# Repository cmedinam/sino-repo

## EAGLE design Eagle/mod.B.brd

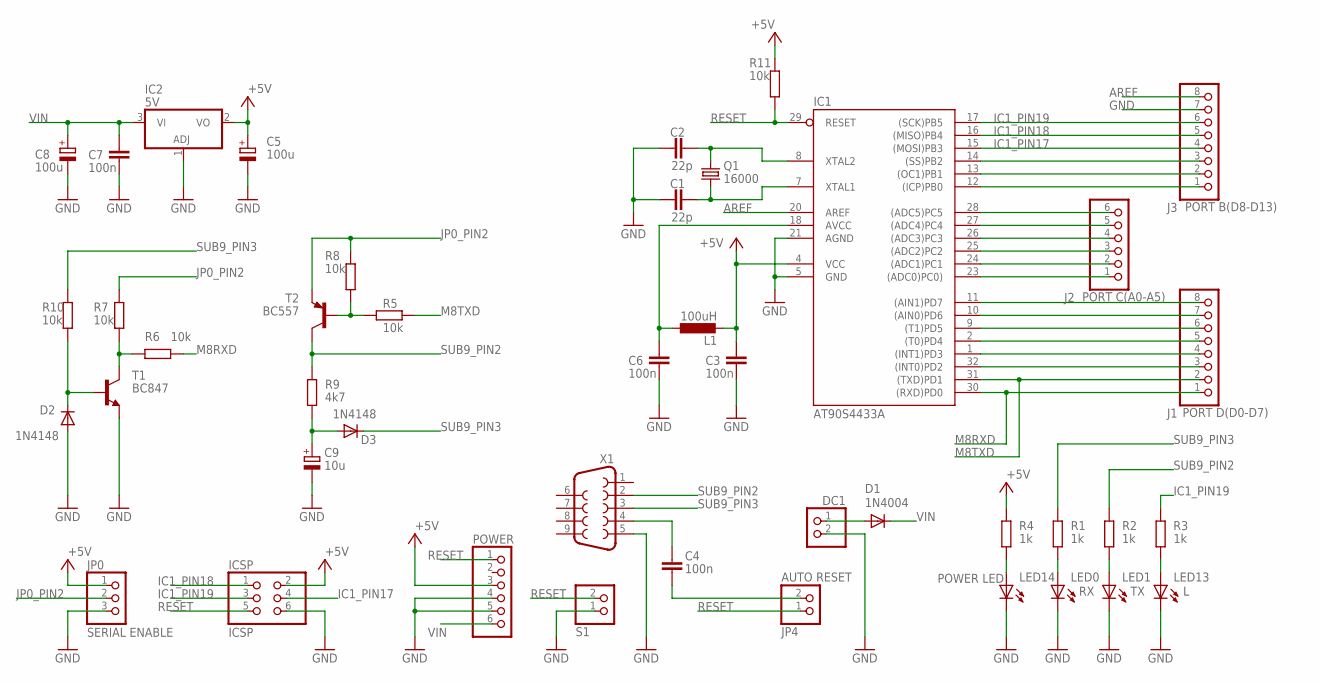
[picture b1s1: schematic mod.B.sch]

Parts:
C1, C2: 22p; C0805
C3, C4, C6, C7: 100n; C0805
C5, C8: 100u; PANASONIC_D
C9: 10u; PANASONIC_B
D1: 1N4004; SOD80C
D2, D3: 1N4148; SOD80C
DC1: PINHD-1X2; 1X02
IC1: AT90S4433A; TQFP32-08
IC2: 5V; SOT223
ICSP: ICSP; 2X03
J1: PORT D(D0-D7); 1X08
J2: PORT C(A0-A5); 1X06
J3: PORT B(D8-D13); 1X08
JP0: SERIAL ENABLE; 1X03
JP4: AUTO RESET; 1X02
L1: 100uH; L1812
LED0: RX; CHIP-LED0603
LED1: TX; CHIP-LED0603
LED13: L; CHIP-LED0603
LED14: POWER LED; CHIP-LED0603
POWER: PINHD-1X6; 1X06
Q1: 16000; SM49
R1, R2, R3, R4: 1k; M0805
R5, R6, R7, R8, R10, R11: 10k; M0805
R9: 4k7; R1206
S1: PINHD-1X2; 1X02
T1: BC847; SOT23
T2: BC557; SOT23-BEC
X1: F09H

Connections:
+5V: C3.1, C5.+, IC1.4 (VCC), IC2.2 (VO), ICSP.2, JP0.1, L1.2, POWER.3, R4.1, R11.2
AREF: IC1.20 (AREF), J3.8
GND: C1.1, C2.1, C3.2, C5.-, C6.2, C7.2, C8.-, C9.-, D2.A, DC1.2, IC1.5 (GND), IC1.21 (AGND), IC2.1 (ADJ), ICSP.6, J3.7, JP0.3, LED0.C, LED1.C, LED13.C, LED14.C, POWER.4, POWER.5, S1.1, T1.2 (E), X1.5
IC1_PIN17: IC1.15 ((MOSI)PB3), ICSP.4, J3.4
IC1_PIN18: IC1.16 ((MISO)PB4), ICSP.1, J3.5
IC1_PIN19: IC1.17 ((SCK)PB5), ICSP.3, J3.6, R3.1
JP0_PIN2: JP0.2, R7.2, R8.2, T2.E
M8RXD: IC1.30 ((RXD)PD0), J1.1, R6.1
M8TXD: IC1.31 ((TXD)PD1), J1.2, R5.2
unnamed: IC1.28 ((ADC5)PC5), J2.6
unnamed: IC1.27 ((ADC4)PC4), J2.5
unnamed: IC1.26 ((ADC3)PC3), J2.4
unnamed: IC1.25 ((ADC2)PC2), J2.3
unnamed: IC1.24 ((ADC1)PC1), J2.2
unnamed: IC1.23 ((ADC0)PC0)), J2.1
unnamed: IC1.11 ((AIN1)PD7), J1.8
unnamed: IC1.10 ((AIN0)PD6), J1.7
unnamed: IC1.9 ((T1)PD5), J1.6
unnamed: IC1.2 ((T0)PD4), J1.5
unnamed: IC1.1 ((INT1)PD3), J1.4
unnamed: IC1.32 ((INT0)PD2), J1.3
unnamed: LED14.A, R4.2
unnamed: R5.1, R8.1, T2.B
unnamed: IC1.12 ((ICP)PB0), J3.1
unnamed: IC1.13 ((OC1)PB1), J3.2
unnamed: IC1.14 ((SS)PB2), J3.3
unnamed: LED13.A, R3.2
unnamed: C4.1, X1.4
unnamed: LED1.A, R2.1
unnamed: C9.+, D3.A, R9.1
unnamed: D1.A, DC1.1
unnamed: C4.2, JP4.2
unnamed: D2.C, R10.1, T1.1 (B)
unnamed: R6.2, R7.1, T1.3 (C)
unnamed: LED0.A, R1.1
unnamed: C1.2, IC1.7 (XTAL1), Q1.1
unnamed: C2.2, IC1.8 (XTAL2), Q1.2
unnamed: C6.1, IC1.18 (AVCC), L1.1
RESET: IC1.29 (RESET), ICSP.5, JP4.1, POWER.1, R11.1, S1.2
SUB9_PIN2: R2.2, R9.2, T2.C, X1.2
SUB9_PIN3: D3.C, R1.2, R10.2, X1.3
VIN: C7.1, C8.+, D1.C, IC2.3 (VI), POWER.6

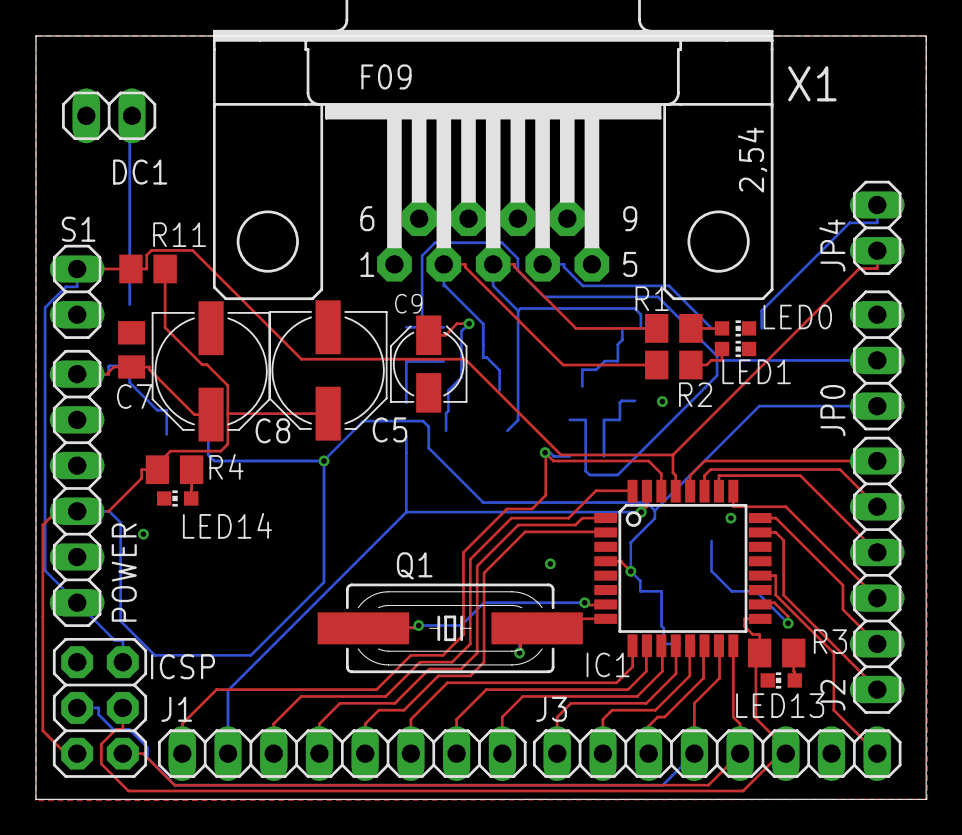
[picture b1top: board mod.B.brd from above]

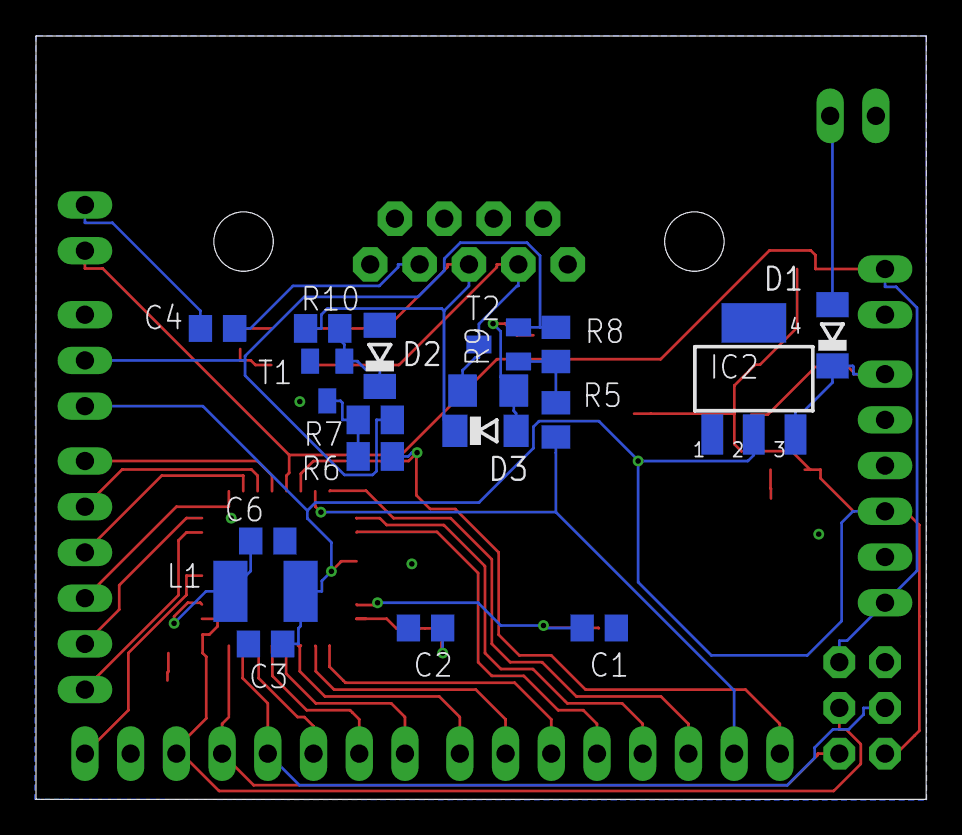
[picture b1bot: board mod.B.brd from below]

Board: 2 copper layers, 49.5 x 42.4 mm, 43 parts (18 on the bottom side), 42 nets.

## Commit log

2016-05-06 Adding README.md - First commit
2016-05-06 Make init files structure
    To organize de repository, a file structure is implemented.
    The file structure is:
    On root:
    Eagle ::A folder to save eagle files .brd .sch .epf
    Gerber ::To save de diferent gerber files for every manufacturer(in a new folder).
    Documentation ::Where board and project info is located.
2016-05-06 Design of handmade manufactured PCB
    It has been designed on Eagle.
    Customized components are include on custom libraries added to Eagle/lib
    Photolites had already generated.
    Waiting for testing and making a report over documentation.
2016-05-06 Design for manufacturing(SeeedStudio). It has been designed on Eagle. Customized components are include on custom libraries added to Eagle/lib Gerber files had already generated for send to SeeedStud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
2016-05-06 Rename Eagle/drl to Eagle/dru, the right name
2016-05-06 Renamed Mod.B dru for identify that one to merge
